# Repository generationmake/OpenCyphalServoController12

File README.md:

# OpenCyphalServoController12
Board to control up to 12 servos with a Raspberry Pi Pico to connect via CAN using OpenCyphal and UCANPHY Micro

## Description

### analog measurements

| **channel** | **usage**       | **range**  |
|:-----------:|:---------------:|:----------:|
| ADC0        | battery voltage | 0 - 66 V   |
| ADC1        | servo voltage   | 0 - 6.6 V  |
| ADC2        | CAN bus voltage | 0 - 6.6 V  |

### power supply

The power for the microcontroller and the CAN interface can be fed via the CAN connector or thepower regulator for the servos. The power regulator for the servos can be enabled and disabled by the microcontroller to save power in stand-by.

input voltage: 10 - 40 V

## PCB

### Top

### Bottom

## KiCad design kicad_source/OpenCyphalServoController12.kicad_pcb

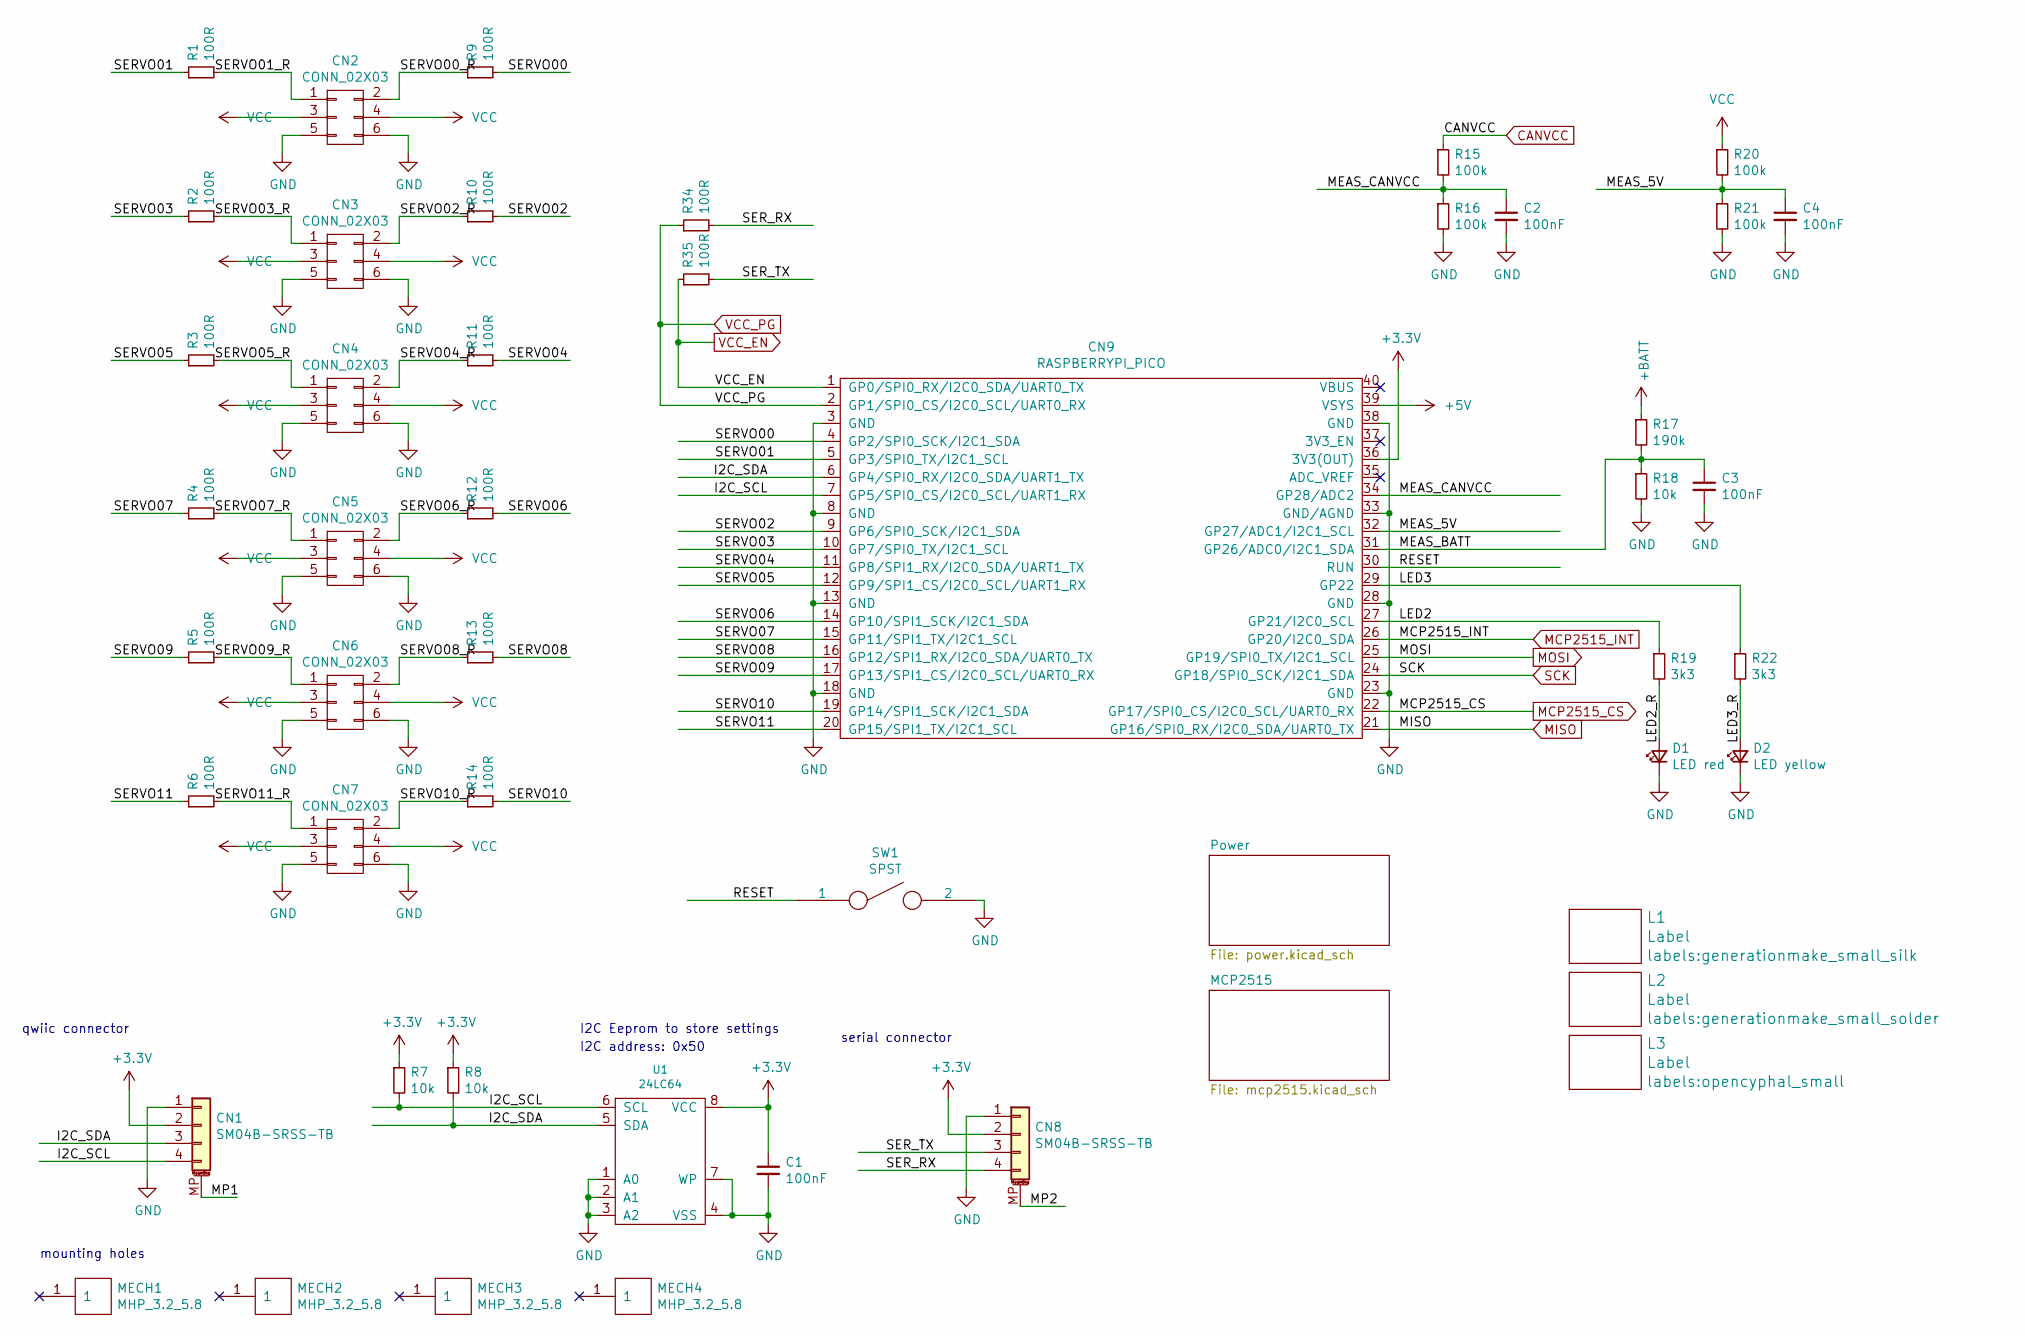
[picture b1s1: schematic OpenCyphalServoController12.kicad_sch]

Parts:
C1, C2, C3, C4: 100nF; C_0603_1608Metric
CN1, CN8: SM04B-SRSS-TB; JST_SH_SM04B-SRSS-TB_1x04-1MP_P1.00mm_Horizontal
CN2, CN3, CN4, CN5, CN6, CN7: CONN_02X03; PinHeader_2x03_P2.54mm_Horizontal
CN9: RASPBERRYPI_PICO; RASPI_PICO_SOLDER_Kopie
D1: LED red; LED_0603_1608Metric
D2: LED yellow; LED_0603_1608Metric
L1: Label; generationmake_small_silk
L2: Label; generationmake_small_solder
L3: Label; opencyphal_small
MECH1, MECH2, MECH3, MECH4: MHP_3.2_5.8
R1, R2, R3, R4, R5, R6, R9, R10, R11, R12, R13, R14, R34, R35: 100R; R_0603_1608Metric
R7, R8, R18: 10k; R_0603_1608Metric
R15, R16, R20, R21: 100k; R_0603_1608Metric
R17: 190k; R_0603_1608Metric
R19, R22: 3k3; R_0603_1608Metric
SW1: SPST; SW_SPST_CK_RS282G05A3
U1: 24LC64; SOIC-8_3.9x4.9mm_P1.27mm

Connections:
+3V3: C1.1, CN1.2, CN8.2, CN9.36 (3V3(OUT)), R7.1, R8.1, U1.8 (VCC); also elsewhere on the board
+5V: CN9.39 (VSYS); also elsewhere on the board
+BATT: R17.1; also elsewhere on the board
/I2C_SCL: CN1.4, CN9.7 (GP5/SPI0_CS/I2C0_SCL/UART1_RX), R7.2, U1.6 (SCL)
/I2C_SDA: CN1.3, CN9.6 (GP4/SPI0_RX/I2C0_SDA/UART1_TX), R8.2, U1.5 (SDA)
/LED2: CN9.27 (GP21/I2C0_SCL), R19.1
/LED2_R: D1.2 (A), R19.2
/LED3: CN9.29 (GP22), R22.1
/LED3_R: D2.2 (A), R22.2
/MEAS_5V: C4.1, CN9.32 (GP27/ADC1/I2C1_SCL), R20.2, R21.1
/MEAS_BATT: C3.1, CN9.31 (GP26/ADC0/I2C1_SDA), R17.2, R18.1
/MEAS_CANVCC: C2.1, CN9.34 (GP28/ADC2), R15.2, R16.1
/MP1: CN1.MP (MountPin)
/MP2: CN8.MP (MountPin)
/RESET: CN9.30 (RUN), SW1.1
/SERVO00: CN9.4 (GP2/SPI0_SCK/I2C1_SDA), R9.2
/SERVO00_R: CN2.2, R9.1
/SERVO01: CN9.5 (GP3/SPI0_TX/I2C1_SCL), R1.1
/SERVO01_R: CN2.1, R1.2
/SERVO02: CN9.9 (GP6/SPI0_SCK/I2C1_SDA), R10.2
/SERVO02_R: CN3.2, R10.1
/SERVO03: CN9.10 (GP7/SPI0_TX/I2C1_SCL), R2.1
/SERVO03_R: CN3.1, R2.2
/SERVO04: CN9.11 (GP8/SPI1_RX/I2C0_SDA/UART1_TX), R11.2
/SERVO04_R: CN4.2, R11.1
/SERVO05: CN9.12 (GP9/SPI1_CS/I2C0_SCL/UART1_RX), R3.1
/SERVO05_R: CN4.1, R3.2
/SERVO06: CN9.14 (GP10/SPI1_SCK/I2C1_SDA), R12.2
/SERVO06_R: CN5.2, R12.1
/SERVO07: CN9.15 (GP11/SPI1_TX/I2C1_SCL), R4.1
/SERVO07_R: CN5.1, R4.2
/SERVO08: CN9.16 (GP12/SPI1_RX/I2C0_SDA/UART0_TX), R13.2
/SERVO08_R: CN6.2, R13.1
/SERVO09: CN9.17 (GP13/SPI1_CS/I2C0_SCL/UART0_RX), R5.1
/SERVO09_R: CN6.1, R5.2
/SERVO10: CN9.19 (GP14/SPI1_SCK/I2C1_SDA), R14.2
/SERVO10_R: CN7.2, R14.1
/SERVO11: CN9.20 (GP15/SPI1_TX/I2C1_SCL), R6.1
/SERVO11_R: CN7.1, R6.2
/SER_RX: CN8.4, R34.2
/SER_TX: CN8.3, R35.2
CANVCC: R15.1; also elsewhere on the board
GND: C1.2, C2.2, C3.2, C4.2, CN1.1, CN2.5, CN2.6, CN3.5, CN3.6, CN4.5, CN4.6, CN5.5, CN5.6, CN6.5, CN6.6, CN7.5, CN7.6, CN8.1, CN9.3 (GND), CN9.8 (GND), CN9.13 (GND), CN9.18 (GND), CN9.23 (GND), CN9.28 (GND), CN9.33 (GND/AGND), CN9.38 (GND), D1.1 (K), D2.1 (K), R16.2, R18.2, R21.2, SW1.2, U1.1 (A0), U1.2 (A1), U1.3 (A2), U1.4 (VSS), U1.7 (WP); also elsewhere on the board
MCP2515_CS: CN9.22 (GP17/SPI0_CS/I2C0_SCL/UART0_RX); also elsewhere on the board
MCP2515_INT: CN9.26 (GP20/I2C0_SDA); also elsewhere on the board
MISO: CN9.21 (GP16/SPI0_RX/I2C0_SDA/UART0_TX); also elsewhere on the board
MOSI: CN9.25 (GP19/SPI0_TX/I2C1_SCL); also elsewhere on the board
SCK: CN9.24 (GP18/SPI0_SCK/I2C1_SDA); also elsewhere on the board
VCC: CN2.3, CN2.4, CN3.3, CN3.4, CN4.3, CN4.4, CN5.3, CN5.4, CN6.3, CN6.4, CN7.3, CN7.4, R20.1; also elsewhere on the board
VCC_EN: CN9.1 (GP0/SPI0_RX/I2C0_SDA/UART0_TX), R35.1; also elsewhere on the board
VCC_PG: CN9.2 (GP1/SPI0_CS/I2C0_SCL/UART0_RX), R34.1; also elsewhere on the board

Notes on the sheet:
serial connector
qwiic connector
mounting holes
I2C address: 0x50
I2C Eeprom to store settings

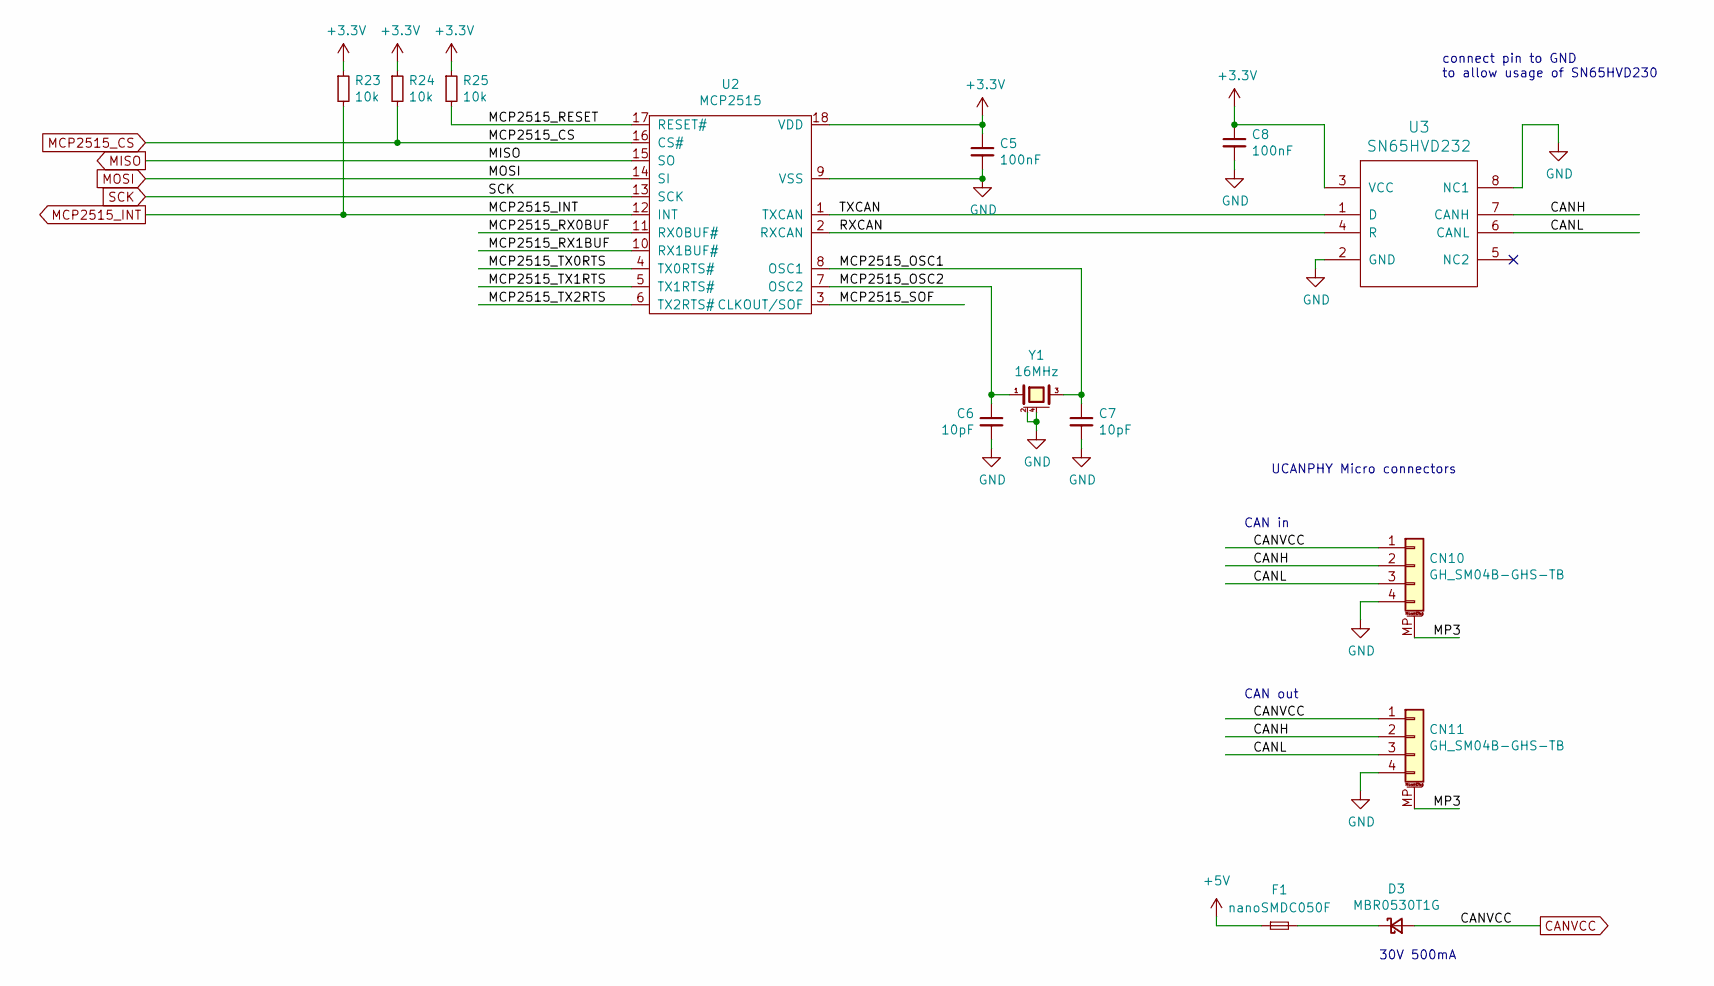
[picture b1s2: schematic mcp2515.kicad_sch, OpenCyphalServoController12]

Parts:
C5, C8: 100nF; C_0603_1608Metric
C6, C7: 10pF; C_0603_1608Metric
CN10, CN11: GH_SM04B-GHS-TB; JST_GH_SM04B-GHS-TB_1x04-1MP_P1.25mm_Horizontal
D3: MBR0530T1G; D_SOD-123
F1: nanoSMDC050F; Fuse_1206_3216Metric
R23, R24, R25: 10k; R_0603_1608Metric
U2: MCP2515; SOIC-18W_7.5x11.6mm_P1.27mm
U3: SN65HVD232; SOIC-8_3.9x4.9mm_P1.27mm
Y1: 16MHz; Crystal_SMD_3.2x2.5mm_4Pad

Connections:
+3V3: C5.1, C8.1, R23.1, R24.1, R25.1, U2.18 (VDD), U3.3 (VCC); also elsewhere on the board
+5V: F1.1; also elsewhere on the board
/MCP2515/CANH: CN10.2, CN11.2, U3.7 (CANH)
/MCP2515/CANL: CN10.3, CN11.3, U3.6 (CANL)
/MCP2515/MCP2515_OSC1: C7.1, U2.8 (OSC1), Y1.3
/MCP2515/MCP2515_OSC2: C6.1, U2.7 (OSC2), Y1.1
/MCP2515/MCP2515_RESET: R25.2, U2.17 (RESET#)
/MCP2515/MCP2515_RX0BUF: U2.11 (RX0BUF#)
/MCP2515/MCP2515_RX1BUF: U2.10 (RX1BUF#)
/MCP2515/MCP2515_SOF: U2.3 (CLKOUT/SOF)
/MCP2515/MCP2515_TX0RTS: U2.4 (TX0RTS#)
/MCP2515/MCP2515_TX1RTS: U2.5 (TX1RTS#)
/MCP2515/MCP2515_TX2RTS: U2.6 (TX2RTS#)
/MCP2515/MP3: CN10.MP (MountPin), CN11.MP (MountPin)
/MCP2515/RXCAN: U2.2 (RXCAN), U3.4 (R)
/MCP2515/TXCAN: U2.1 (TXCAN), U3.1 (D)
CANVCC: CN10.1, CN11.1, D3.2 (A); also elsewhere on the board
GND: C5.2, C6.2, C7.2, C8.2, CN10.4, CN11.4, U2.9 (VSS), U3.2 (GND), U3.8 (NC1), Y1.2 (case), Y1.4 (case); also elsewhere on the board
MCP2515_CS: R24.2, U2.16 (CS#); also elsewhere on the board
MCP2515_INT: R23.2, U2.12 (INT); also elsewhere on the board
MISO: U2.15 (SO); also elsewhere on the board
MOSI: U2.14 (SI); also elsewhere on the board
unnamed: D3.1 (K), F1.2
SCK: U2.13 (SCK); also elsewhere on the board

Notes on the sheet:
connect pin to GND to allow usage of SN65HVD230
UCANPHY Micro connectors
30V 500mA
CAN in
CAN out

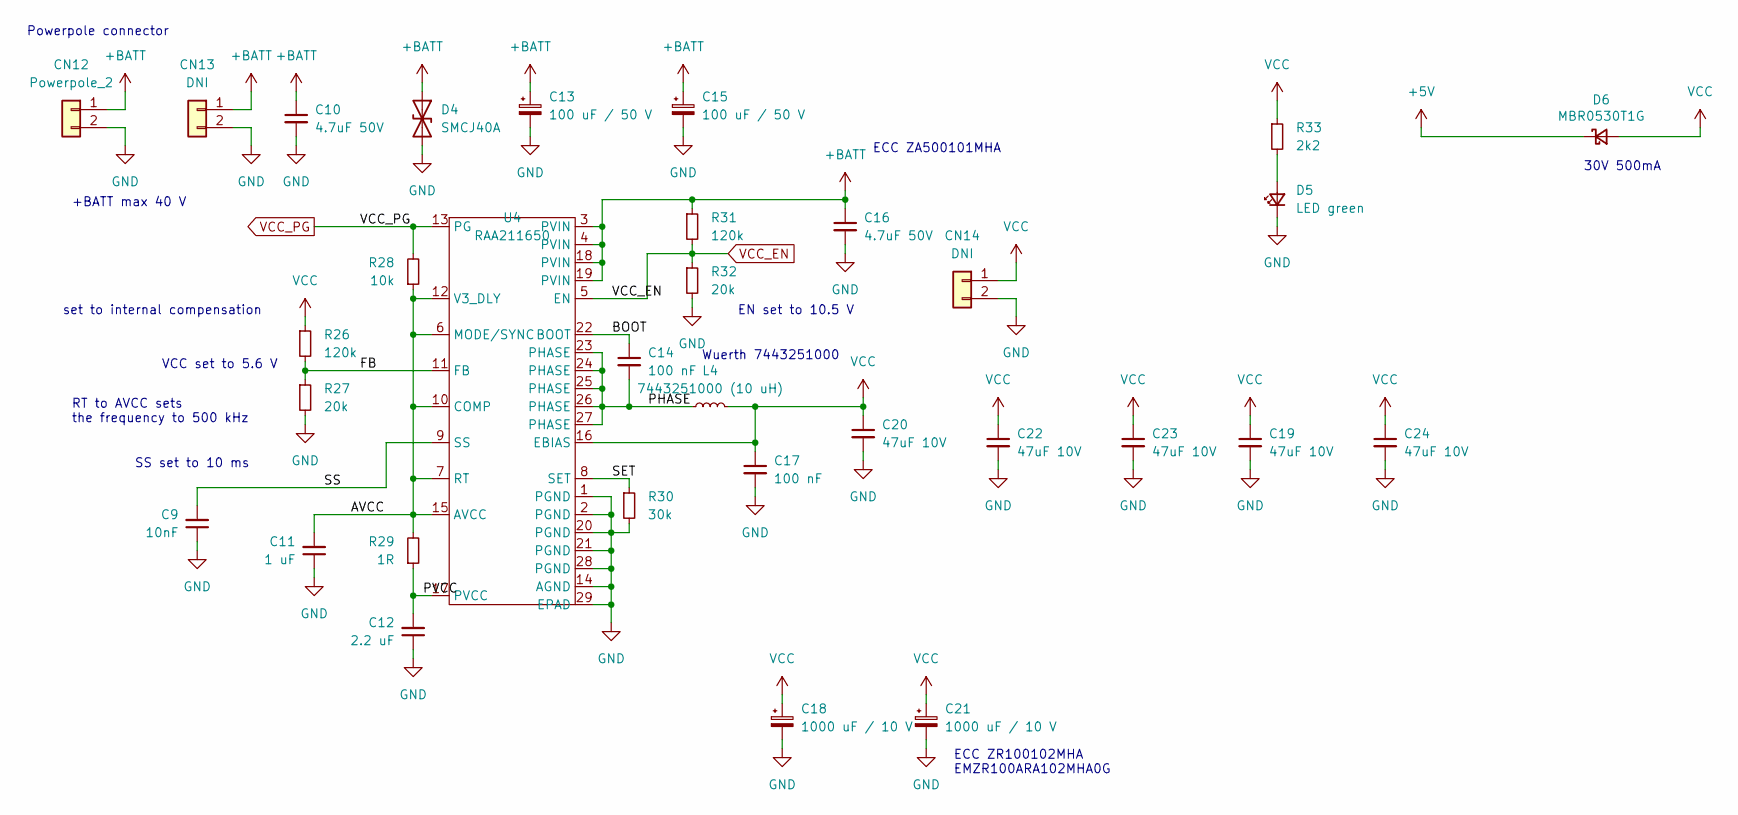
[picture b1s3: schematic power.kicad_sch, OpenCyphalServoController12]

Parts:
C9: 10nF; C_0603_1608Metric
C10, C16: 4.7uF 50V; C_1210_3225Metric
C11: 1 uF; C_0603_1608Metric
C12: 2.2 uF; C_0603_1608Metric
C13, C15: 100 uF / 50 V; CP_Elec_8x10
C14, C17: 100 nF; C_0603_1608Metric
C18, C21: 1000 uF / 10 V; CP_Elec_8x10
C19, C20, C22, C23, C24: 47uF 10V; C_1210_3225Metric
CN12: Powerpole_2; POWERPOLE_hor_2
CN13: DNI; PhoenixContact_MC_1,5_2-G-3.5_1x02_P3.50mm_Horizontal
CN14: DNI; PinHeader_1x02_P2.54mm_Vertical
D4: SMCJ40A; D_SMC
D5: LED green; LED_0603_1608Metric
D6: MBR0530T1G; D_SOD-123
L4: 7443251000 (10 uH); L_Wuerth_HCI-1050
R26, R31: 120k; R_0603_1608Metric
R27, R32: 20k; R_0603_1608Metric
R28: 10k; R_0603_1608Metric
R29: 1R; R_0603_1608Metric
R30: 30k; R_0603_1608Metric
R33: 2k2; R_0603_1608Metric
U4: RAA211650; QFN-28-1EP_4x5mm_P0.5mm_EP2.65x3.65mm

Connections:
+5V: D6.1 (K); also elsewhere on the board
+BATT: C10.1, C13.1, C15.1, C16.1, CN12.1, CN13.1, D4.1 (A1), R31.1, U4.3 (PVIN), U4.4 (PVIN), U4.18 (PVIN), U4.19 (PVIN); also elsewhere on the board
/Power/AVCC: C11.2, R28.1, R29.2, U4.6 (MODE/SYNC), U4.7 (RT), U4.10 (COMP), U4.12 (V3_DLY), U4.15 (AVCC)
/Power/BOOT: C14.1, U4.22 (BOOT)
/Power/FB: R26.2, R27.1, U4.11 (FB)
/Power/PHASE: C14.2, L4.1, U4.23 (PHASE), U4.24 (PHASE), U4.25 (PHASE), U4.26 (PHASE), U4.27 (PHASE)
/Power/PVCC: C12.2, R29.1, U4.17 (PVCC)
/Power/SET: R30.1, U4.8 (SET)
/Power/SS: C9.2, U4.9 (SS)
GND: C9.1, C10.2, C11.1, C12.1, C13.2, C15.2, C16.2, C17.2, C18.2, C19.2, C20.2, C21.2, C22.2, C23.2, C24.2, CN12.2, CN13.2, CN14.2, D4.2 (A2), D5.1 (K), R27.2, R30.2, R32.2, U4.1 (PGND), U4.2 (PGND), U4.14 (AGND), U4.20 (PGND), U4.21 (PGND), U4.28 (PGND), U4.29 (EPAD); also elsewhere on the board
unnamed: D5.2 (A), R33.2
VCC: C17.1, C18.1, C19.1, C20.1, C21.1, C22.1, C23.1, C24.1, CN14.1, D6.2 (A), L4.2, R26.1, R33.1, U4.16 (EBIAS); also elsewhere on the board
VCC_EN: R31.2, R32.1, U4.5 (EN); also elsewhere on the board
VCC_PG: R28.2, U4.13 (PG); also elsewhere on the board

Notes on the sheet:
Wuerth 7443251000
EN set to 10.5 V
+BATT max 40 V
ECC ZR100102MHA EMZR100ARA102MHA0G
set to internal compensation
ECC ZA500101MHA
RT to AVCC sets the frequency to 500 kHz
30V 500mA
VCC set to 5.6 V
Powerpole connector
SS set to 10 ms

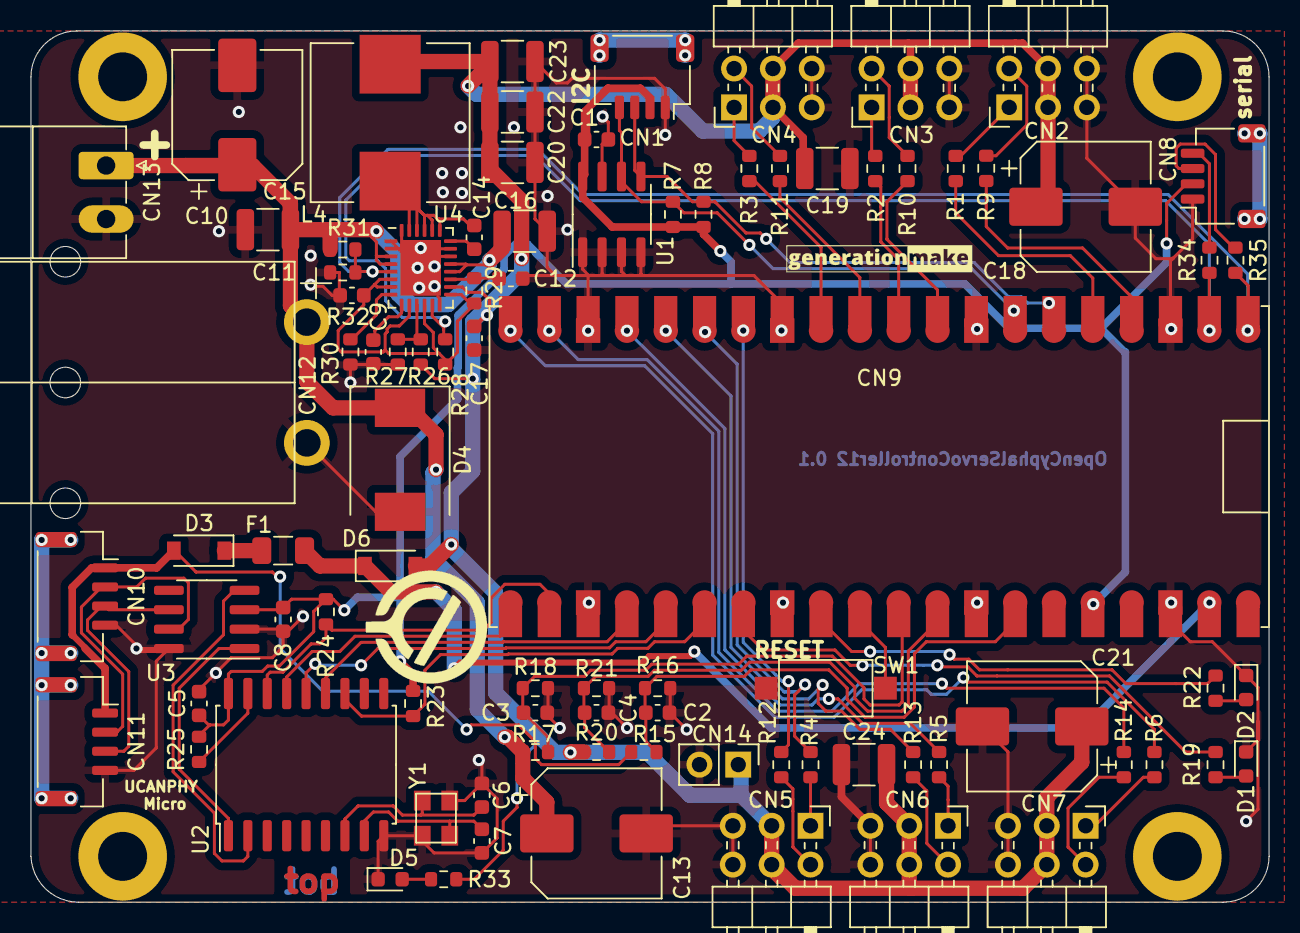
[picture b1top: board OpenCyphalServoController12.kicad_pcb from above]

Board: 2 copper layers, 81.0 x 57.0 mm, 94 parts (1 on the bottom side), 66 nets.

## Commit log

2023-01-22 added kicad project
2023-01-22 renamed project files
2023-01-23 reworked schematic
2023-02-01 started first placement
2023-02-01 started layout
2023-02-01 added images
2023-02-01 added pdf schematic
2023-02-02 corrected resistor dividers for voltage measurement
2023-02-03 added additional capacitors on VCC
2023-02-03 added enable and power good for voltage regulator
2023-02-04 added mounting pads, beautified layout, run DRC
2023-02-04 updated schematic pdf, updated images
